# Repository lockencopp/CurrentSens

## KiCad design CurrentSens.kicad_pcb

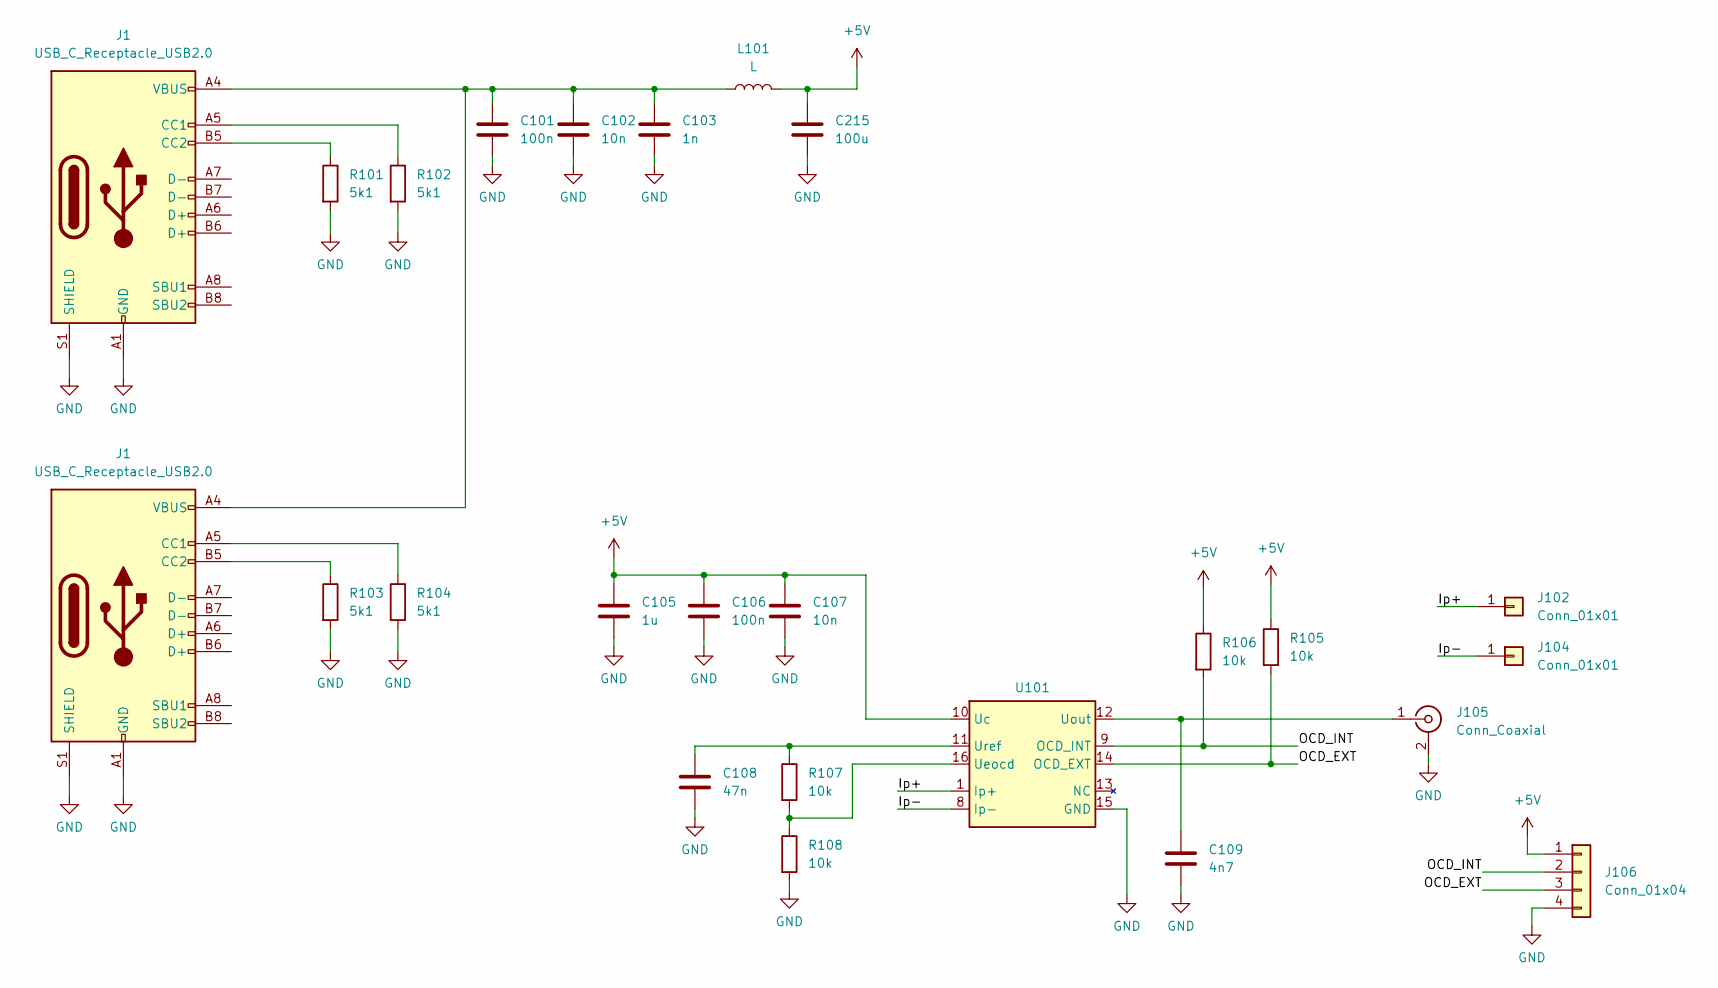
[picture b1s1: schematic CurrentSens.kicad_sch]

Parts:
C101, C106: 100n; C_0805_2012Metric_Pad1.18x1.45mm_HandSolder
C102, C107: 10n; C_0805_2012Metric_Pad1.18x1.45mm_HandSolder
C103: 1n; C_0805_2012Metric_Pad1.18x1.45mm_HandSolder
C105: 1u; C_0805_2012Metric_Pad1.18x1.45mm_HandSolder
C108: 47n; C_0805_2012Metric_Pad1.18x1.45mm_HandSolder
C109: 4n7; C_0805_2012Metric_Pad1.18x1.45mm_HandSolder
C215: 100u; C_Elec_6.3x7.7
J1: USB_C_Receptacle_USB2.0; USB_C_Receptacle_HRO_TYPE-C-31-M-12
J102, J104: Conn_01x01; PB4
J105: Conn_Coaxial; BNC_Amphenol_B6252HB-NPP3G-50_Horizontal
J106: Conn_01x04; PinHeader_1x04_P2.54mm_Vertical
L101: L; SDR0604330KL
R101, R102, R103, R104: 5k1; R_0805_2012Metric_Pad1.20x1.40mm_HandSolder
R105, R106, R107, R108: 10k; R_0805_2012Metric_Pad1.20x1.40mm_HandSolder
U101: LEM_HMSR

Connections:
+5V: C105.1, C106.1, C107.1, J106.1, L101.2, R105.1, R106.1, U101.10 (Uc); also elsewhere on the board
/Ip+: J102.1, U101.1 (Ip+)
/Ip-: J104.1, U101.8 (Ip-)
/OCD_EXT: J106.3, R105.2, U101.14 (OCD_EXT)
/OCD_INT: J106.2, R106.2, U101.9 (OCD_INT)
GND: C101.2, C102.2, C103.2, C105.2, C106.2, C107.2, C108.2, C109.2, J105.2 (Ext), J106.4, R101.2, R102.2, R103.2, R104.2, R108.2, U101.15 (GND); also elsewhere on the board
unnamed 6: C101.1, C102.1, C103.1, L101.1; also elsewhere on the board
unnamed 7: R102.1; also elsewhere on the board
unnamed 8: R101.1; also elsewhere on the board
unnamed 9: R104.1; also elsewhere on the board
unnamed 10: R103.1; also elsewhere on the board
unnamed: C109.1, J105.1 (In), U101.12 (Uout)
unnamed: R107.2, R108.1, U101.16 (Ueocd)
unnamed: C108.1, R107.1, U101.11 (Uref)

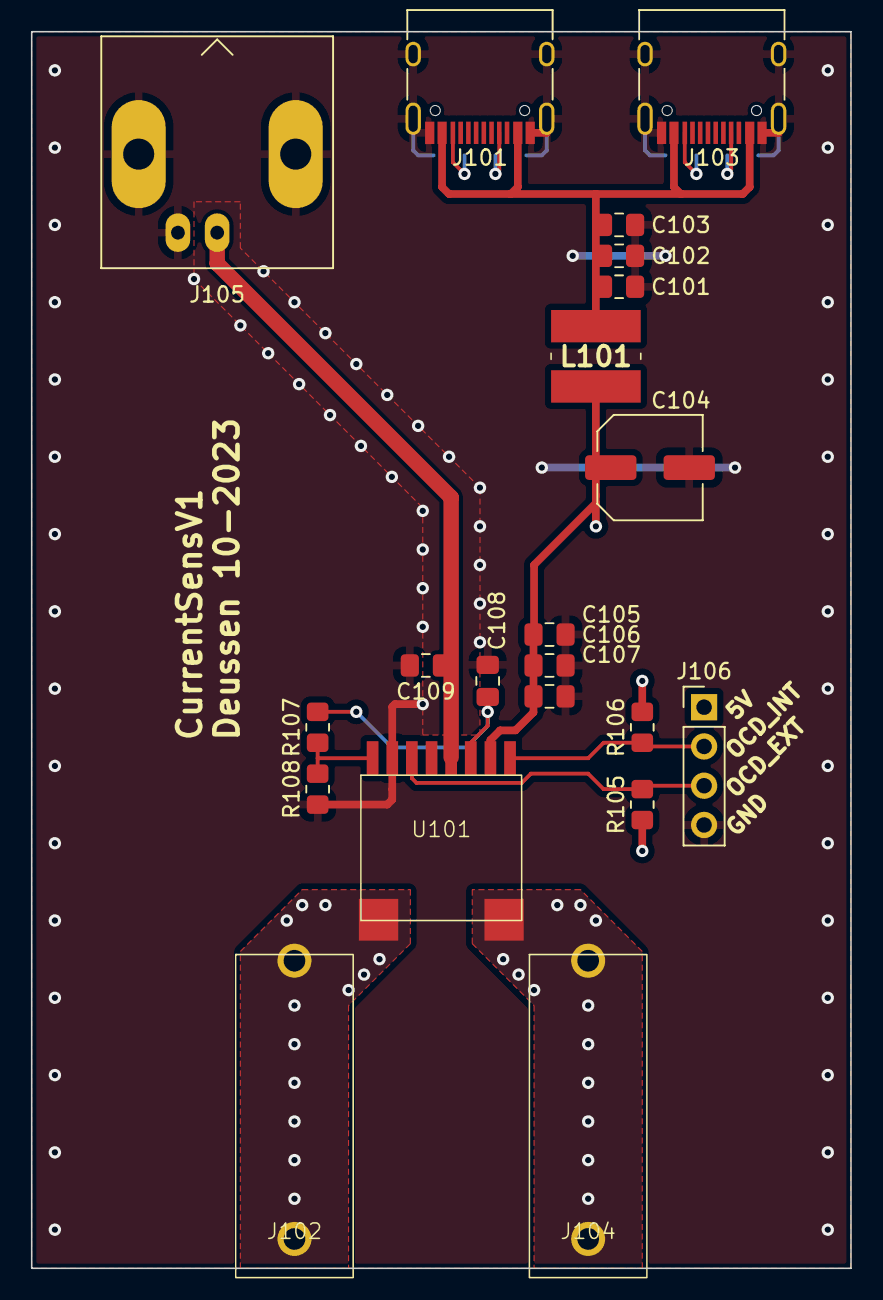
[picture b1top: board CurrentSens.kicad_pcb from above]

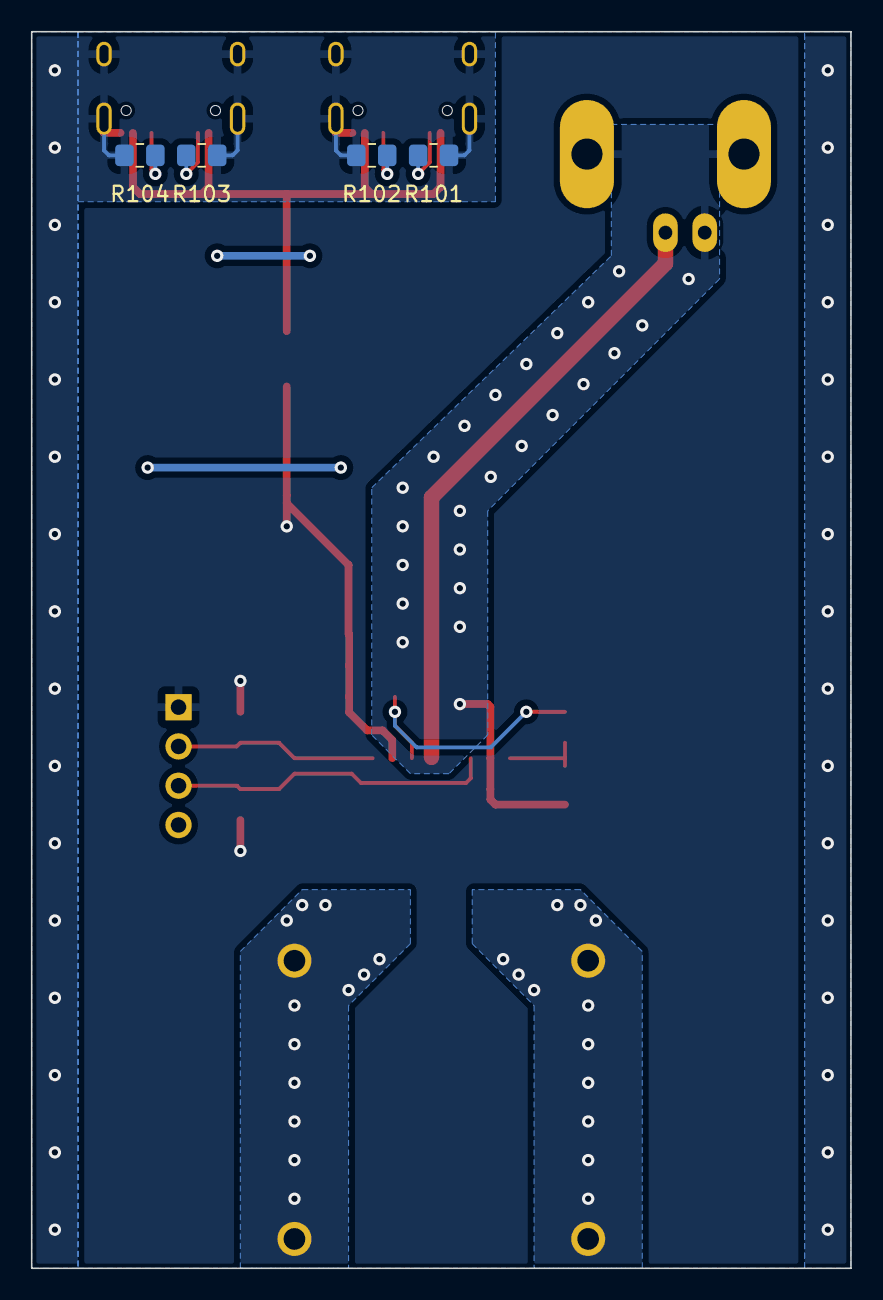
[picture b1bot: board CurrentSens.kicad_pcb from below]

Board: 2 copper layers, 53.0 x 80.0 mm, 25 parts (4 on the bottom side), 14 nets.

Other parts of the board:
C104: 100u; C_Elec_6.3x7.7
J101, J103: USB_C_Receptacle_USB2.0; USB_C_Receptacle_HRO_TYPE-C-31-M-12

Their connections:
+5V: C104.1; also elsewhere on the board
GND: C104.2, J101.A1 (GND), J101.A12 (GND), J101.B1 (GND), J101.B12 (GND), J101.S1 (SHIELD), J103.A1 (GND), J103.A12 (GND), J103.B1 (GND), J103.B12 (GND), J103.S1 (SHIELD); also elsewhere on the board
unnamed 6: J101.A4 (VBUS), J101.A9 (VBUS), J101.B4 (VBUS), J101.B9 (VBUS), J103.A4 (VBUS), J103.A9 (VBUS), J103.B4 (VBUS), J103.B9 (VBUS); also elsewhere on the board
unnamed 7: J101.A5 (CC1); also elsewhere on the board
unnamed 8: J101.B5 (CC2); also elsewhere on the board
unnamed 9: J103.A5 (CC1); also elsewhere on the board
unnamed 10: J103.B5 (CC2); also elsewhere on the board

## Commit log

2023-10-23 First version for production run at aisler
2023-10-23 Some fixes for first production run at aisler - change inductor - add 3D data - fix references in silkscreen
2023-10-23 Adjust position of BNC jack
2023-10-24 Update BNC jack model
